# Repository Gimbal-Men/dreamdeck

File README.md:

# Dreamdeck

Hackboard for the normal PC use with colored lights around the Boarder.
Additional has it 3 state Lights and one Encoder.

3d Printed Case:

List:
1x Seeed XIAO RP2040
12x MX-Style switches
1x EC11 Rotary encoders
12x Blank DSA keycaps
16x SK6812 MINI-E LEDs
4x M3x16mm screws
4x M3x5mx4mm heatset inserts
1x 3d Printed Case

Softwear in develpopement

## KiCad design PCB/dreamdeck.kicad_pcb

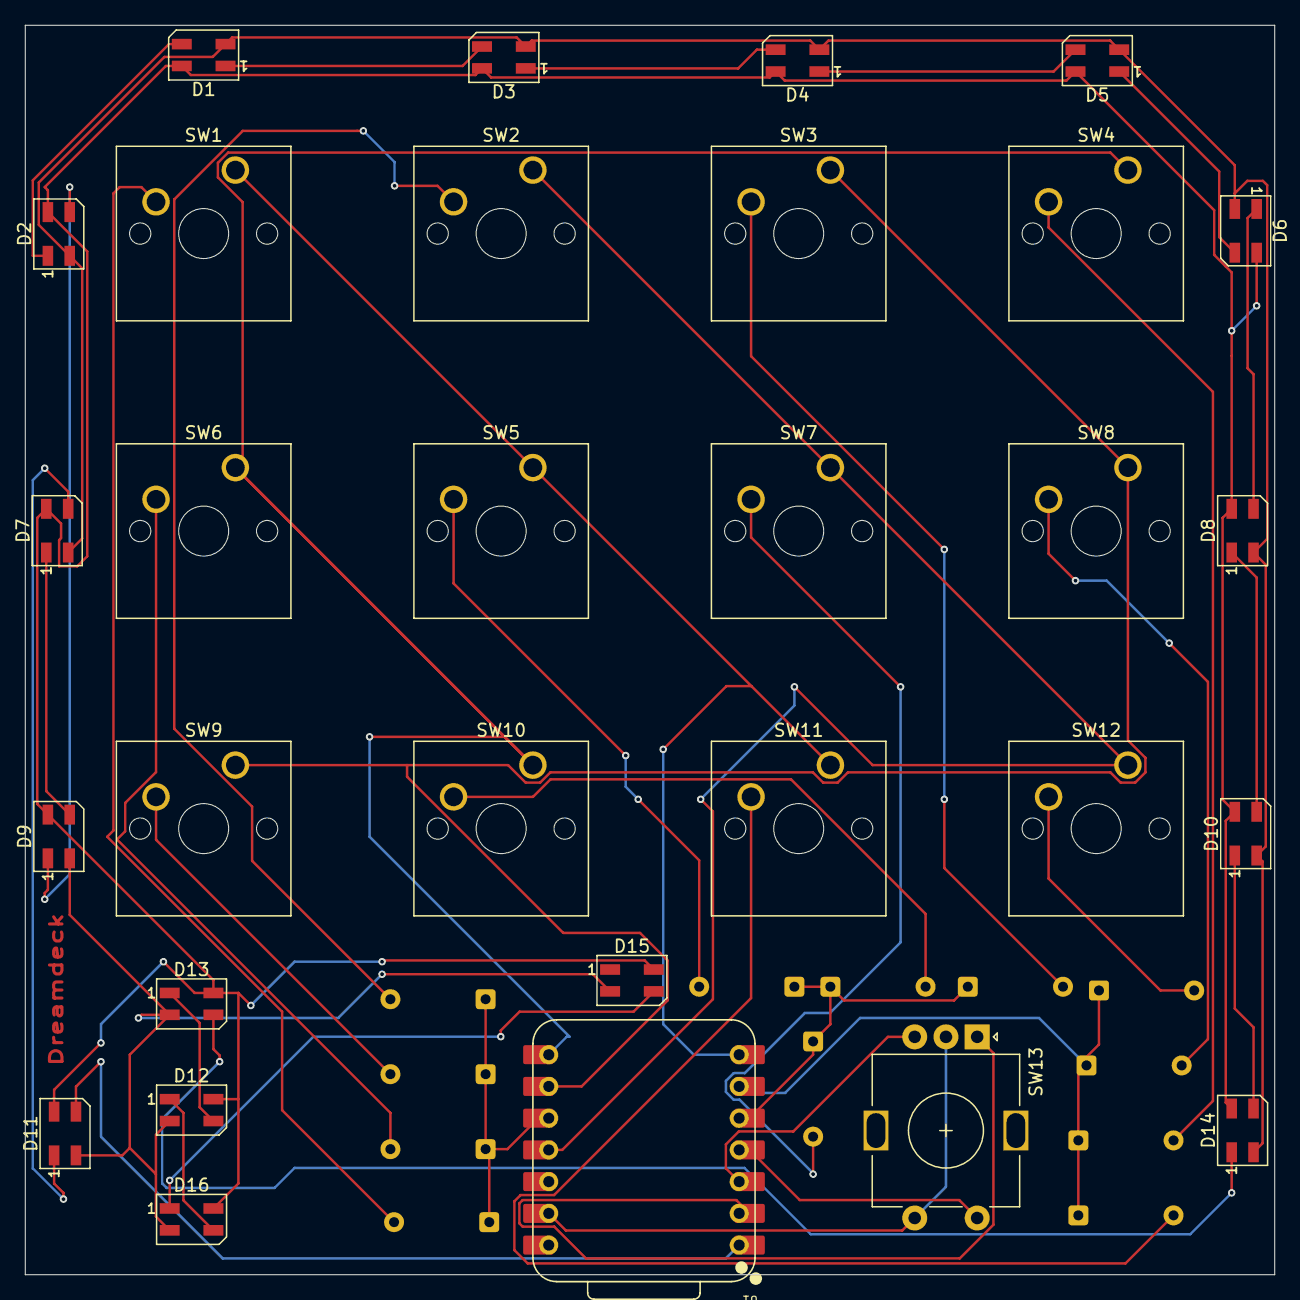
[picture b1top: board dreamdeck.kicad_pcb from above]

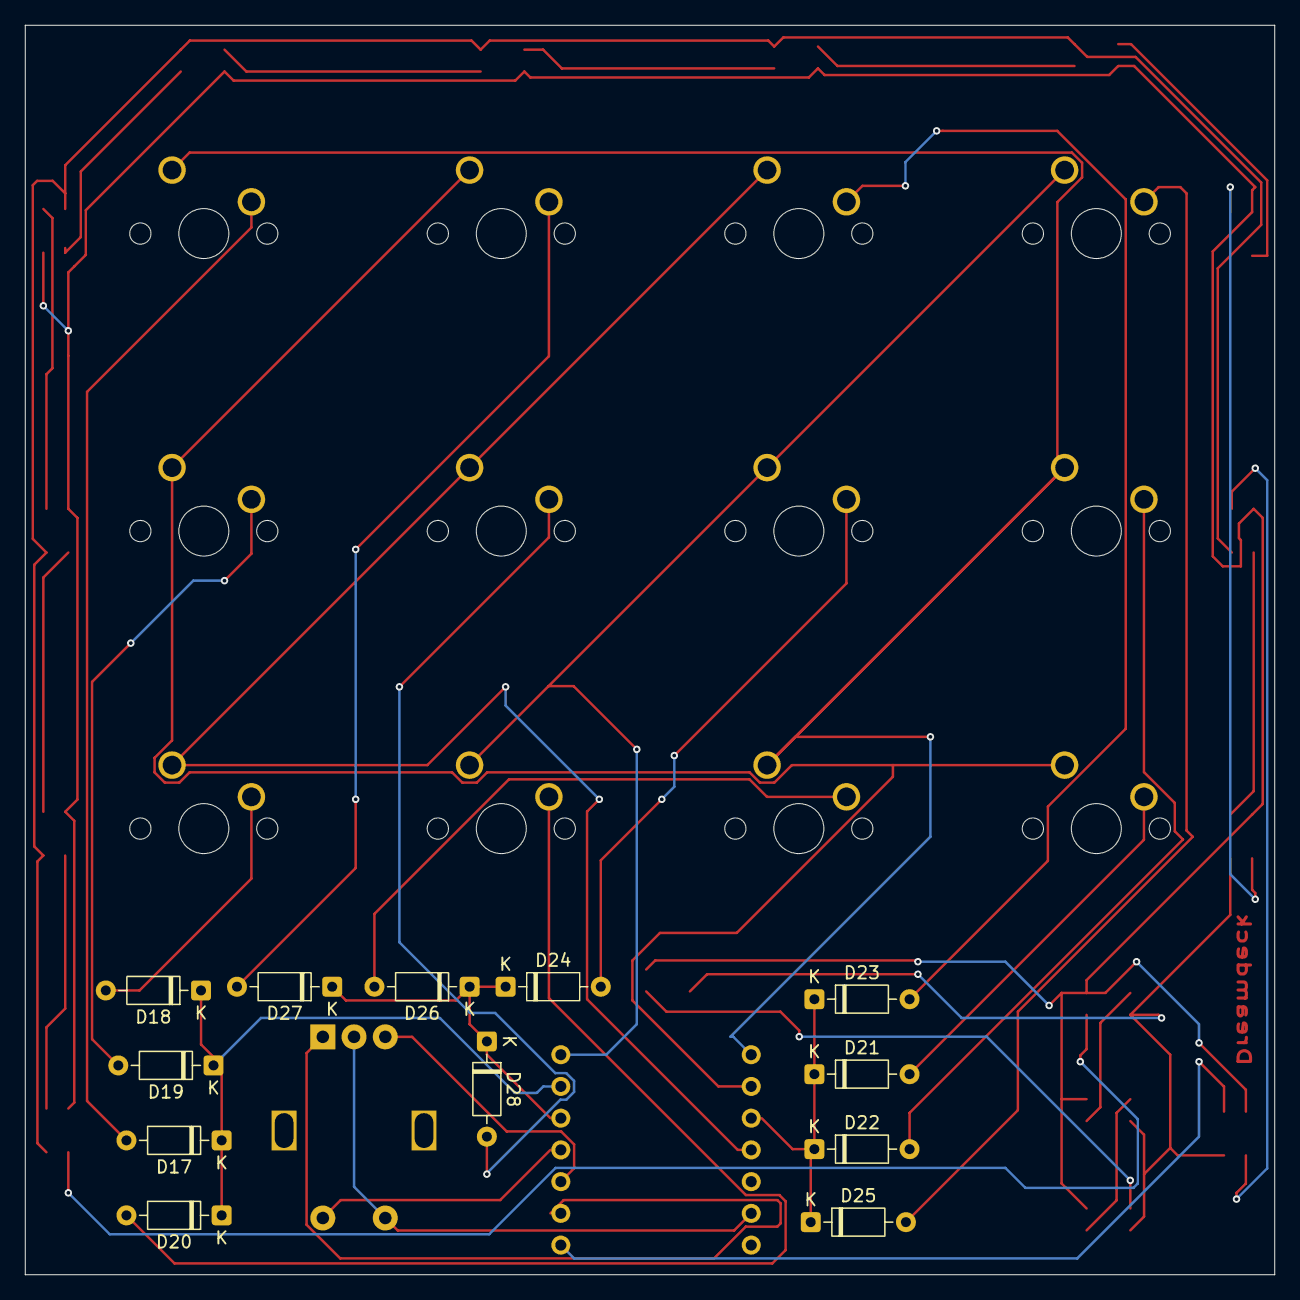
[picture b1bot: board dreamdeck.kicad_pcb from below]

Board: 2 copper layers, 100.0 x 100.0 mm, 42 parts (12 on the bottom side), 41 nets.

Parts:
D1, D2, D3, D4, D5, D6, D7, D8, D9, D10, D11, D12, D13, D14, D15, D16: SK6812MINI; LED_SK6812MINI_PLCC4_3.5x3.5mm_P1.75mm
D17, D18, D19, D20, D21, D22, D23, D24, D25, D26, D27, D28: 1N4148; D_DO-35_SOD27_P7.62mm_Horizontal
SW1, SW2, SW3, SW4, SW5, SW6, SW7, SW8, SW9, SW10, SW11, SW12: SW_Push; SW_Cherry_MX_1.00u_PCB
SW13: RotaryEncoder_Switch; RotaryEncoder_Alps_EC11E-Switch_Vertical_H20mm
U1: XIAO-RP2040-DIP

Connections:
/Col 1: SW1.1, SW5.1, SW11.1, U1.7 (GPIO0/TX)
/Col 2: SW4.1, SW6.1, SW10.1, U1.8 (GPIO1/RX)
/Col 3: SW3.1, SW8.1, SW9.1, U1.9 (GPIO2/SCK)
/Col 4: SW2.1, SW7.1, SW12.1, U1.11 (GPIO3/MOSI)
/Row1: D21.1 (K), D22.1 (K), D23.1 (K), D25.1 (K), U1.10 (GPIO4/MISO)
/Row 2: D24.1 (K), D26.1 (K), D27.1 (K), D28.1 (K), U1.5 (GPIO6/SDA)
/Row 3: D17.1 (K), D18.1 (K), D19.1 (K), D20.1 (K), U1.6 (GPIO7/SCL)
GND: SW13.C, SW13.S1, U1.13 (GND)
unnamed: D25.2 (A), SW1.2
unnamed: D22.2 (A), SW6.2
unnamed: D21.2 (A), SW9.2
unnamed: D23.2 (A), SW2.2
unnamed: D24.2 (A), SW5.2
unnamed: D26.2 (A), SW10.2
unnamed: D27.2 (A), SW3.2
unnamed: D28.2 (A), SW7.2
unnamed: D20.2 (A), SW11.2
unnamed: D17.2 (A), SW4.2
unnamed: D19.2 (A), SW8.2
unnamed: D18.2 (A), SW12.2
unnamed: D11.3 (DIN), U1.1 (GPIO26/ADC0/A0)
unnamed: D7.3 (DIN), D11.1 (DOUT)
unnamed: D1.4 (VDD), D2.4 (VDD), D3.4 (VDD), D4.4 (VDD), D5.4 (VDD), D6.4 (VDD), D7.4 (VDD), D8.4 (VDD), D9.4 (VDD), D10.4 (VDD), D11.4 (VDD), D12.4 (VDD), D13.4 (VDD), D14.4 (VDD), D15.4 (VDD), D16.4 (VDD)
unnamed: D1.2 (VSS), D2.2 (VSS), D3.2 (VSS), D4.2 (VSS), D5.2 (VSS), D6.2 (VSS), D7.2 (VSS), D8.2 (VSS), D9.2 (VSS), D10.2 (VSS), D11.2 (VSS), D12.2 (VSS), D13.2 (VSS), D14.2 (VSS), D15.2 (VSS), D16.2 (VSS)
unnamed: D7.1 (DOUT), D9.3 (DIN)
unnamed: D2.3 (DIN), D9.1 (DOUT)
unnamed: D1.3 (DIN), D2.1 (DOUT)
unnamed: D1.1 (DOUT), D3.3 (DIN)
unnamed: D3.1 (DOUT), D4.3 (DIN)
unnamed: D4.1 (DOUT), D5.3 (DIN)
unnamed: D5.1 (DOUT), D6.3 (DIN)
unnamed: D6.1 (DOUT), D8.3 (DIN)
unnamed: D8.1 (DOUT), D10.3 (DIN)
unnamed: D10.1 (DOUT), D14.3 (DIN)
unnamed: D13.3 (DIN), D14.1 (DOUT)
unnamed: D12.3 (DIN), D13.1 (DOUT)
unnamed: D12.1 (DOUT), D16.3 (DIN)
unnamed: D15.3 (DIN), D16.1 (DOUT)
unnamed: SW13.A, U1.2 (GPIO27/ADC1/A1)
unnamed: SW13.B, U1.3 (GPIO28/ADC2/A2)
unnamed: SW13.S2, U1.4 (GPIO29/ADC3/A3)
